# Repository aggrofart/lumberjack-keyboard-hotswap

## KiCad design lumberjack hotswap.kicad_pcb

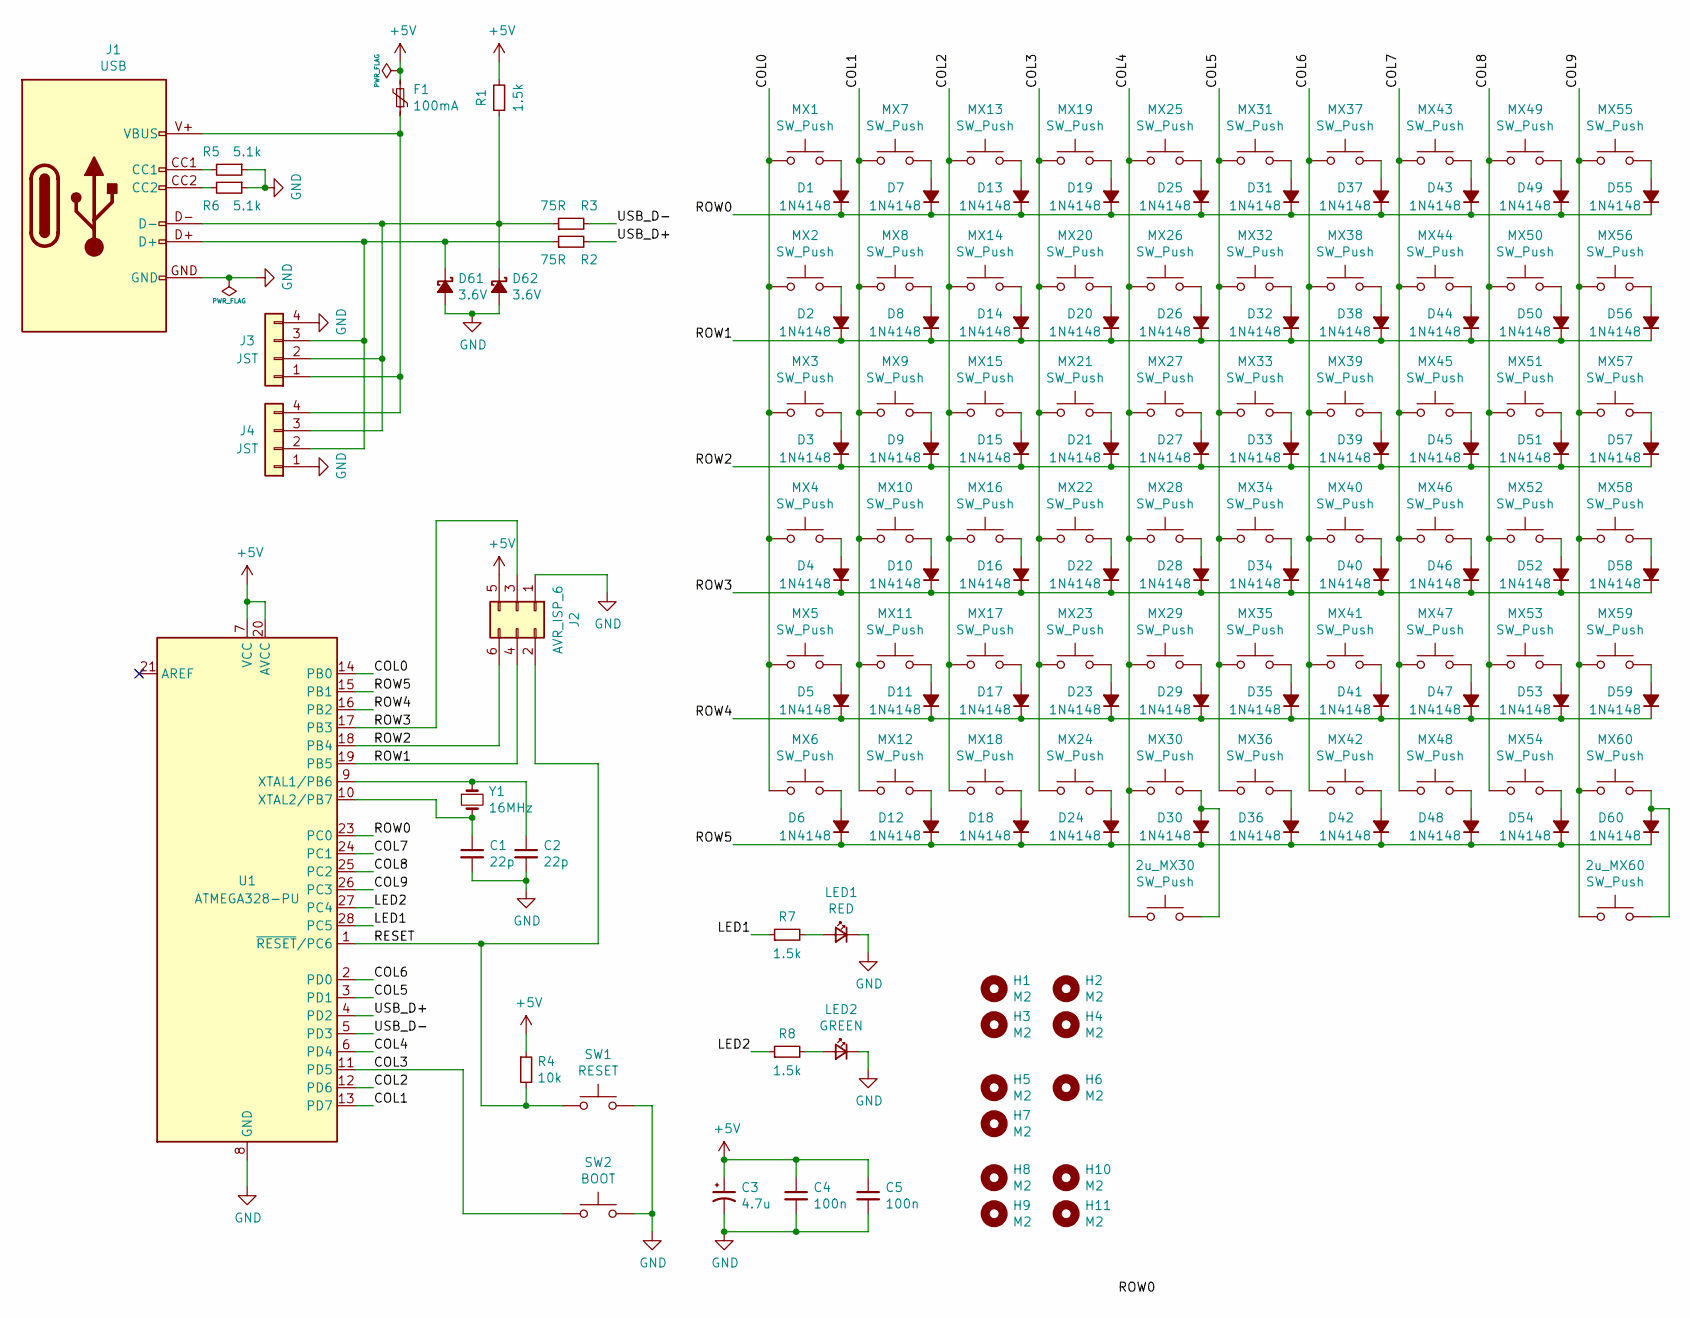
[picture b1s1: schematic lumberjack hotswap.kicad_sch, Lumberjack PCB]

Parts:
2u_MX30, 2u_MX60: SW_Push; MX_PCB_200B
C1, C2: 22p; C_Disc_D3.0mm_W1.6mm_P2.50mm
C3: 4.7u; CP_Radial_D4.0mm_P1.50mm
C4, C5: 100n; C_Disc_D4.3mm_W1.9mm_P5.00mm
D1, D2, D3, D4, D5, D6, D7, D8, D9, D10, D11, D12, D13, D14, D15, D16, D17, D18, D19, D20, D21, D22, D23, D24, D25, D26, D27, D28, D29, D30, D31, D32, D33, D34, D35, D36, D37, D38, D39, D40, D41, D42, D43, D44, D45, D46, D47, D48, D49, D50, D51, D52, D53, D54, D55, D56, D57, D58, D59, D60: 1N4148; D_DO-35_SOD27_P7.62mm_Horizontal
D61, D62: 3.6V; D_DO-35_SOD27_P7.62mm_Horizontal
F1: 100mA; Fuse_Bourns_MF-RHT100
H1, H2, H3, H4, H8, H9, H10, H11: M2; MountingHole_M2
H5, H6, H7: M2; MountingSlot_M2
J1: USB; USB_Hybrid
J2: AVR_ISP_6; PinHeader_2x03_P2.54mm_Vertical
J3: JST; JST_SH_SM04B-SRSS-TB_1x04-1MP_P1.00mm_Horizontal
J4: JST; S4B-ZRLFSN
LED1: RED; LED_D3.0mm
LED2: GREEN; LED_D3.0mm
MX1, MX2, MX3, MX4, MX5, MX6, MX7, MX8, MX9, MX10, MX11, MX12, MX13, MX14, MX15, MX16, MX17, MX18, MX19, MX20, MX21, MX22, MX23, MX24, MX25, MX26, MX27, MX28, MX29, MX30, MX31, MX32, MX33, MX34, MX35, MX36, MX37, MX38, MX39, MX40, MX41, MX42, MX43, MX44, MX45, MX46, MX47, MX48, MX49, MX50, MX51, MX52, MX53, MX54, MX55, MX56, MX57, MX58, MX59, MX60: SW_Push; Lumberjack CherryMX_Choc_v1v2_Hotswap Single Side
R1, R7, R8: 1.5k; R_Axial_DIN0204_L3.6mm_D1.6mm_P7.62mm_Horizontal
R2, R3: 75R; R_Axial_DIN0204_L3.6mm_D1.6mm_P7.62mm_Horizontal
R4: 10k; R_Axial_DIN0204_L3.6mm_D1.6mm_P7.62mm_Horizontal
R5, R6: 5.1k; R_Axial_DIN0204_L3.6mm_D1.6mm_P7.62mm_Horizontal
SW1: RESET; SW_PUSH_6mm
SW2: BOOT; SW_PUSH_6mm
U1: ATMEGA328-PU; DIP-28_W7.62mm
Y1: 16MHz; Crystal_HC49-4H_Vertical

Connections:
+5V: C3.1, C4.1, C5.1, F1.2, J2.5, R1.2, R4.1, U1.7 (VCC), U1.20 (AVCC)
/COL0: MX1.2, MX2.2, MX3.2, MX4.2, MX5.2, MX6.2, U1.14 (PB0)
/COL1: MX7.2, MX8.2, MX9.2, MX10.2, MX11.2, MX12.2, U1.13 (PD7)
/COL2: MX13.2, MX14.2, MX15.2, MX16.2, MX17.2, MX18.2, U1.12 (PD6)
/COL3: MX19.2, MX20.2, MX21.2, MX22.2, MX23.2, MX24.2, SW2.1, U1.11 (PD5)
/COL4: 2u_MX30.2, MX25.2, MX26.2, MX27.2, MX28.2, MX29.2, MX30.2, U1.6 (PD4)
/COL5: MX31.2, MX32.2, MX33.2, MX34.2, MX35.2, MX36.2, U1.3 (PD1)
/COL6: MX37.2, MX38.2, MX39.2, MX40.2, MX41.2, MX42.2, U1.2 (PD0)
/COL7: MX43.2, MX44.2, MX45.2, MX46.2, MX47.2, MX48.2, U1.24 (PC1)
/COL8: MX49.2, MX50.2, MX51.2, MX52.2, MX53.2, MX54.2, U1.25 (PC2)
/COL9: 2u_MX60.2, MX55.2, MX56.2, MX57.2, MX58.2, MX59.2, MX60.2, U1.26 (PC3)
/LED1: R7.1, U1.28 (PC5)
/LED2: R8.1, U1.27 (PC4)
/RESET: J2.2, R4.2, SW1.1, U1.1 (~RESET/PC6)
/ROW0: D1.1 (K), D7.1 (K), D13.1 (K), D19.1 (K), D25.1 (K), D31.1 (K), D37.1 (K), D43.1 (K), D49.1 (K), D55.1 (K), U1.23 (PC0)
/ROW1: D2.1 (K), D8.1 (K), D14.1 (K), D20.1 (K), D26.1 (K), D32.1 (K), D38.1 (K), D44.1 (K), D50.1 (K), D56.1 (K), J2.4, U1.19 (PB5)
/ROW2: D3.1 (K), D9.1 (K), D15.1 (K), D21.1 (K), D27.1 (K), D33.1 (K), D39.1 (K), D45.1 (K), D51.1 (K), D57.1 (K), J2.6, U1.18 (PB4)
/ROW3: D4.1 (K), D10.1 (K), D16.1 (K), D22.1 (K), D28.1 (K), D34.1 (K), D40.1 (K), D46.1 (K), D52.1 (K), D58.1 (K), J2.3, U1.17 (PB3)
/ROW4: D5.1 (K), D11.1 (K), D17.1 (K), D23.1 (K), D29.1 (K), D35.1 (K), D41.1 (K), D47.1 (K), D53.1 (K), D59.1 (K), U1.16 (PB2)
/ROW5: D6.1 (K), D12.1 (K), D18.1 (K), D24.1 (K), D30.1 (K), D36.1 (K), D42.1 (K), D48.1 (K), D54.1 (K), D60.1 (K), U1.15 (PB1)
/USB_D+: R2.2, U1.4 (PD2)
/USB_D-: R3.2, U1.5 (PD3)
GND: C1.2, C2.2, C3.2, C4.2, C5.2, D61.2 (A), D62.2 (A), J1.GND, J2.1, J3.4, J4.1, LED1.1 (K), LED2.1 (K), R5.1, R6.1, SW1.2, SW2.2, U1.8 (GND), U1.22 (GND)
unnamed: D1.2 (A), MX1.1
unnamed: D2.2 (A), MX2.1
unnamed: D3.2 (A), MX3.1
unnamed: D4.2 (A), MX4.1
unnamed: D5.2 (A), MX5.1
unnamed: D6.2 (A), MX6.1
unnamed: D7.2 (A), MX7.1
unnamed: D8.2 (A), MX8.1
unnamed: D9.2 (A), MX9.1
unnamed: D10.2 (A), MX10.1
unnamed: D11.2 (A), MX11.1
unnamed: D12.2 (A), MX12.1
unnamed: D13.2 (A), MX13.1
unnamed: D14.2 (A), MX14.1
unnamed: D15.2 (A), MX15.1
unnamed: D16.2 (A), MX16.1
unnamed: D17.2 (A), MX17.1
unnamed: D18.2 (A), MX18.1
unnamed: D19.2 (A), MX19.1
unnamed: D20.2 (A), MX20.1
unnamed: D21.2 (A), MX21.1
unnamed: D22.2 (A), MX22.1
unnamed: D23.2 (A), MX23.1
unnamed: D24.2 (A), MX24.1
unnamed: D25.2 (A), MX25.1
unnamed: D26.2 (A), MX26.1
unnamed: D27.2 (A), MX27.1
unnamed: D28.2 (A), MX28.1
unnamed: D29.2 (A), MX29.1
unnamed: 2u_MX30.1, D30.2 (A), MX30.1
unnamed: D31.2 (A), MX31.1
unnamed: D32.2 (A), MX32.1
unnamed: D33.2 (A), MX33.1
unnamed: D34.2 (A), MX34.1
unnamed: D35.2 (A), MX35.1
unnamed: D36.2 (A), MX36.1
unnamed: D37.2 (A), MX37.1
unnamed: D38.2 (A), MX38.1
unnamed: D39.2 (A), MX39.1
unnamed: D40.2 (A), MX40.1
unnamed: D41.2 (A), MX41.1
unnamed: D42.2 (A), MX42.1
unnamed: D43.2 (A), MX43.1
unnamed: D44.2 (A), MX44.1
unnamed: D45.2 (A), MX45.1
unnamed: D46.2 (A), MX46.1
unnamed: D47.2 (A), MX47.1
unnamed: D48.2 (A), MX48.1
unnamed: D49.2 (A), MX49.1
unnamed: D50.2 (A), MX50.1
unnamed: D51.2 (A), MX51.1
unnamed: D52.2 (A), MX52.1
unnamed: D53.2 (A), MX53.1
unnamed: D54.2 (A), MX54.1
unnamed: D55.2 (A), MX55.1
unnamed: D56.2 (A), MX56.1
unnamed: D57.2 (A), MX57.1
unnamed: D58.2 (A), MX58.1
unnamed: D59.2 (A), MX59.1
unnamed: 2u_MX60.1, D60.2 (A), MX60.1
unnamed: D61.1 (K), J1.D+, J3.3, J4.2, R2.1
unnamed: D62.1 (K), J1.D-, J3.2, J4.3, R1.1, R3.1
unnamed: J1.CC1, R5.2
unnamed: J1.CC2, R6.2
unnamed: F1.1, J1.V+ (VBUS), J3.1, J4.4
unnamed: LED1.2 (A), R7.2
unnamed: LED2.2 (A), R8.2
unnamed: C2.1, U1.9 (XTAL1/PB6), Y1.1
unnamed: C1.1, U1.10 (XTAL2/PB7), Y1.2

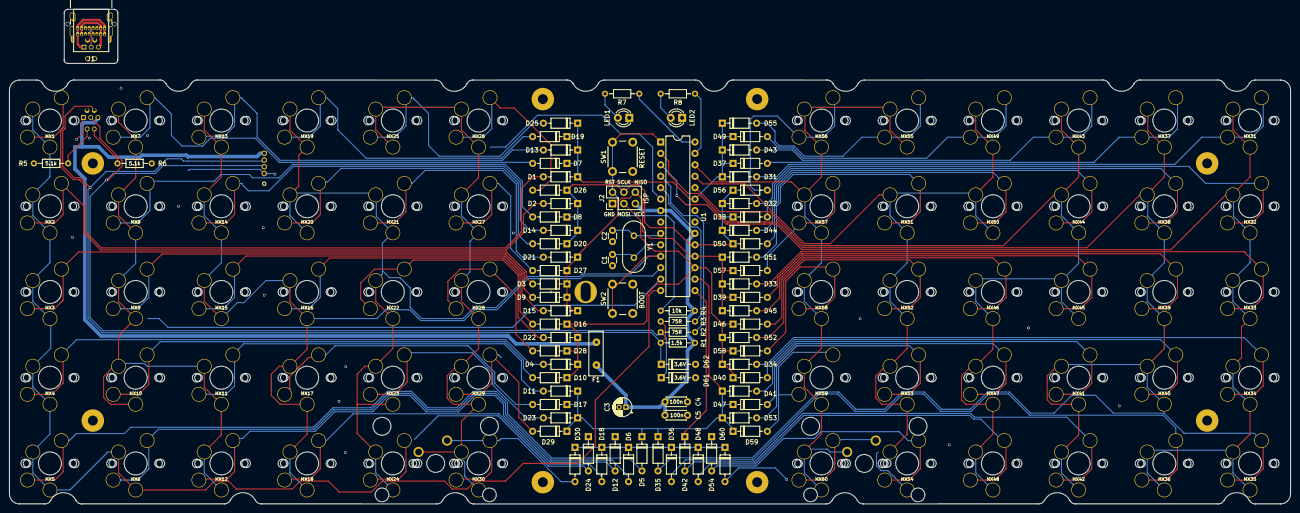
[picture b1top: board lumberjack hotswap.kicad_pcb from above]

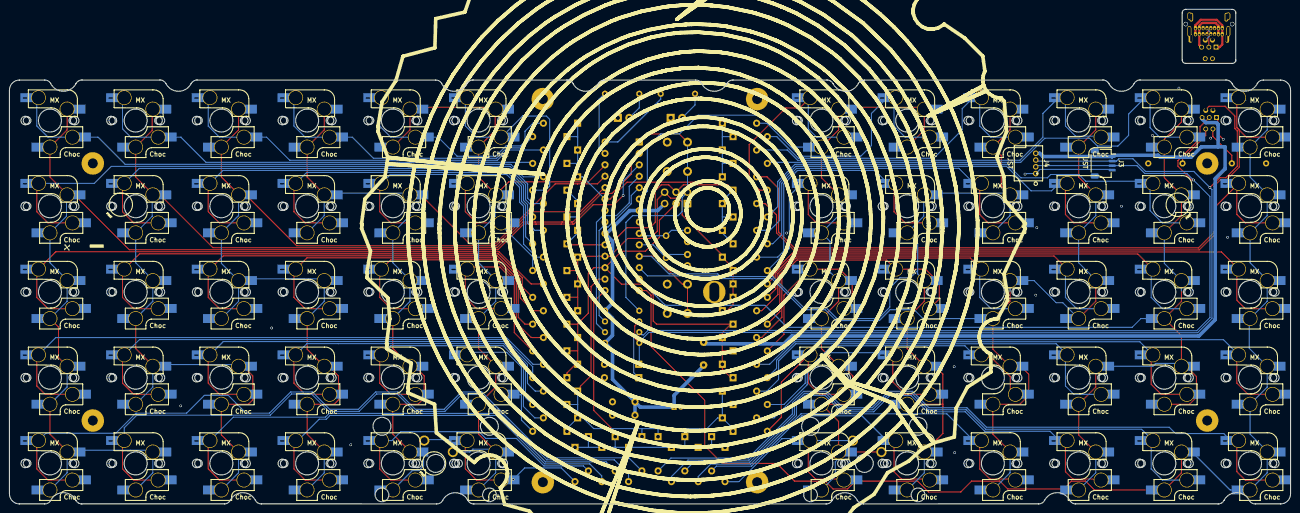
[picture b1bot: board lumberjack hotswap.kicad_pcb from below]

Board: 2 copper layers, 284.7 x 94.2 mm, 159 parts (2 on the bottom side), 92 nets.

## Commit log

2023-04-13 130423 Update
    Finished about 75% of the routing.
2023-04-26 USB C connector
    Updated with USB C connector as a separate board to be soldered on
2023-04-27 Added v3
    v3 changes:
    1. Reversed half of the footprint for the 2 switches nearest the USB C connector
    2. Rerouted the USB C connector pins & removed the USB mini footprint

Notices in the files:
parts and their libraries:
Copyright 2021 Accelerated Designs. All rights reserved.
